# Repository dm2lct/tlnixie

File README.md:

# Schematics and PCB files for the Turmlabor nixie clock kit. 
# Attention: This is a old, buggy version! See the new design on https://github.com/ludwig1992/Nixieclock_kit

Feel free to build your own nixie clock from it.

Features:
  - IN14 nixie tubes but you can adapt many other nixie tubes even if it would not look great
  - ESP12e controller so you can make IoT with it and build your own botnet for world domination if you have enough clocks
  - DS3231 RTC for everyone who does not like IoT and does also not want to be enslaved from AI
  - WS2812B under each nixie tube to make them look more fancy
  - runs from a simple USB charger
  - you can program the controller with your Arduino IDE over USB

But in this version there are a few known issues:

  - wrong footprint of U201 and U202, it should be PQFP44, but of any reason we put TQFP44 on this board. You can solder it but it's not fun. 
  - wrong wiring of U403, you need to wire pin 10 and 11 to pin 18 and 19 and move VCC from pin 18 to pin 20.
  - the high voltage power supply does not work as good as it is supposed to be. This might be a problem with the low input voltage of about 5V

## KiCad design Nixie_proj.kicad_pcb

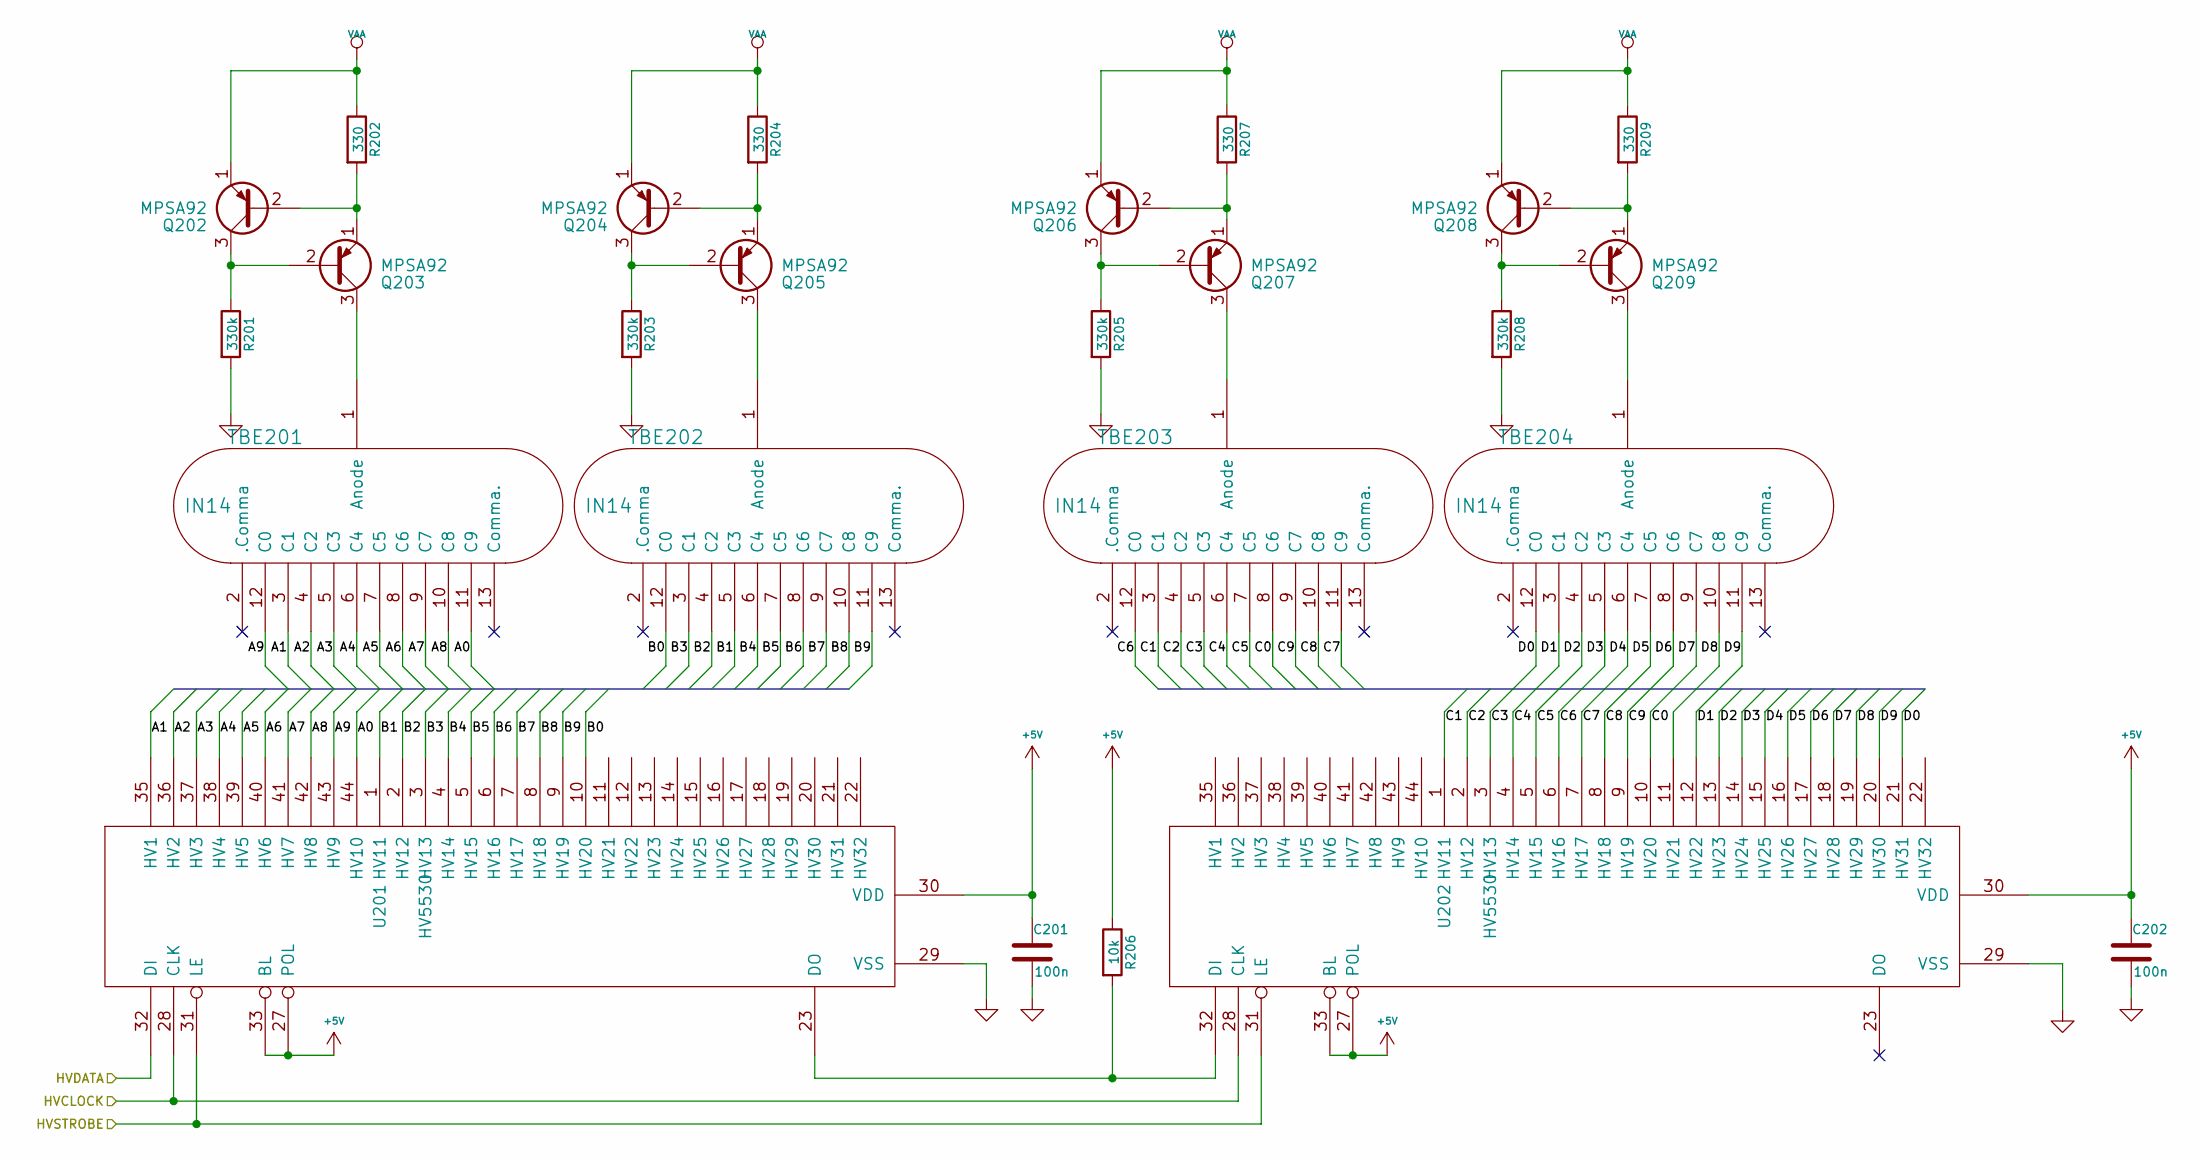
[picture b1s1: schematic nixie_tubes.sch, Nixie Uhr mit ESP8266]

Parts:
C201, C202: 100n; C_0805_HandSoldering
Q202, Q203, Q204, Q205, Q206, Q207, Q208, Q209: MPSA92; TO-92_Molded_Wide_Oval
R201, R203, R205, R208: 330k; R_Axial_DIN0207_L6.3mm_D2.5mm_P10.16mm_Horizontal
R202, R204, R207, R209: 330; R_Axial_DIN0207_L6.3mm_D2.5mm_P10.16mm_Horizontal
R206: 10k; R_0805_HandSoldering
TBE201, TBE202, TBE203, TBE204: IN14; IN-14-mod
U201, U202: HV5530; TQFP-44_10x10mm_Pitch0.8mm

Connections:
+5V: C201.1, C202.1, R206.1, U201.27 (POL), U201.30 (VDD), U201.33 (BL), U202.27 (POL), U202.30 (VDD), U202.33 (BL); also elsewhere on the board
/Microcontroller and clock/HVCLOCK: U201.28 (CLK), U202.28 (CLK); also elsewhere on the board
/Microcontroller and clock/HVDATA: U201.32 (DI); also elsewhere on the board
/Microcontroller and clock/HVSTROBE: U201.31 (LE), U202.31 (LE); also elsewhere on the board
/Tubes with drivers/A0: TBE201.11 (C9), U201.44 (HV10)
/Tubes with drivers/A1: TBE201.3 (C1), U201.35 (HV1)
/Tubes with drivers/A2: TBE201.4 (C2), U201.36 (HV2)
/Tubes with drivers/A3: TBE201.5 (C3), U201.37 (HV3)
/Tubes with drivers/A4: TBE201.6 (C4), U201.38 (HV4)
/Tubes with drivers/A5: TBE201.7 (C5), U201.39 (HV5)
/Tubes with drivers/A6: TBE201.8 (C6), U201.40 (HV6)
/Tubes with drivers/A7: TBE201.9 (C7), U201.41 (HV7)
/Tubes with drivers/A8: TBE201.10 (C8), U201.42 (HV8)
/Tubes with drivers/A9: TBE201.12 (C0), U201.43 (HV9)
/Tubes with drivers/B0: TBE202.12 (C0), U201.10 (HV20)
/Tubes with drivers/B1: TBE202.5 (C3), U201.1 (HV11)
/Tubes with drivers/B2: TBE202.4 (C2), U201.2 (HV12)
/Tubes with drivers/B3: TBE202.3 (C1), U201.3 (HV13)
/Tubes with drivers/B4: TBE202.6 (C4), U201.4 (HV14)
/Tubes with drivers/B5: TBE202.7 (C5), U201.5 (HV15)
/Tubes with drivers/B6: TBE202.8 (C6), U201.6 (HV16)
/Tubes with drivers/B7: TBE202.9 (C7), U201.7 (HV17)
/Tubes with drivers/B8: TBE202.10 (C8), U201.8 (HV18)
/Tubes with drivers/B9: TBE202.11 (C9), U201.9 (HV19)
/Tubes with drivers/C0: TBE203.8 (C6), U202.10 (HV20)
/Tubes with drivers/C1: TBE203.3 (C1), U202.1 (HV11)
/Tubes with drivers/C2: TBE203.4 (C2), U202.2 (HV12)
/Tubes with drivers/C3: TBE203.5 (C3), U202.3 (HV13)
/Tubes with drivers/C4: TBE203.6 (C4), U202.4 (HV14)
/Tubes with drivers/C5: TBE203.7 (C5), U202.5 (HV15)
/Tubes with drivers/C6: TBE203.12 (C0), U202.6 (HV16)
/Tubes with drivers/C7: TBE203.11 (C9), U202.7 (HV17)
/Tubes with drivers/C8: TBE203.10 (C8), U202.8 (HV18)
/Tubes with drivers/C9: TBE203.9 (C7), U202.9 (HV19)
/Tubes with drivers/D0: TBE204.12 (C0), U202.21 (HV31)
/Tubes with drivers/D1: TBE204.3 (C1), U202.12 (HV22)
/Tubes with drivers/D2: TBE204.4 (C2), U202.13 (HV23)
/Tubes with drivers/D3: TBE204.5 (C3), U202.14 (HV24)
/Tubes with drivers/D4: TBE204.6 (C4), U202.15 (HV25)
/Tubes with drivers/D5: TBE204.7 (C5), U202.16 (HV26)
/Tubes with drivers/D6: TBE204.8 (C6), U202.17 (HV27)
/Tubes with drivers/D7: TBE204.9 (C7), U202.18 (HV28)
/Tubes with drivers/D8: TBE204.10 (C8), U202.19 (HV29)
/Tubes with drivers/D9: TBE204.11 (C9), U202.20 (HV30)
GND: C201.2, C202.2, R201.2, R203.2, R205.2, R208.2, U201.29 (VSS), U202.29 (VSS); also elsewhere on the board
unnamed: Q202.2 (B), Q203.1 (E), R202.2
unnamed: Q202.3 (C), Q203.2 (B), R201.1
unnamed: Q203.3 (C), TBE201.1 (Anode)
unnamed: Q204.2 (B), Q205.1 (E), R204.2
unnamed: Q204.3 (C), Q205.2 (B), R203.1
unnamed: Q205.3 (C), TBE202.1 (Anode)
unnamed: Q206.2 (B), Q207.1 (E), R207.2
unnamed: Q206.3 (C), Q207.2 (B), R205.1
unnamed: Q207.3 (C), TBE203.1 (Anode)
unnamed: Q208.2 (B), Q209.1 (E), R209.2
unnamed: Q208.3 (C), Q209.2 (B), R208.1
unnamed: Q209.3 (C), TBE204.1 (Anode)
unnamed: R206.2, U201.23 (DO), U202.32 (DI)
VAA: Q202.1 (E), Q204.1 (E), Q206.1 (E), Q208.1 (E), R202.1, R204.1, R207.1, R209.1; also elsewhere on the board

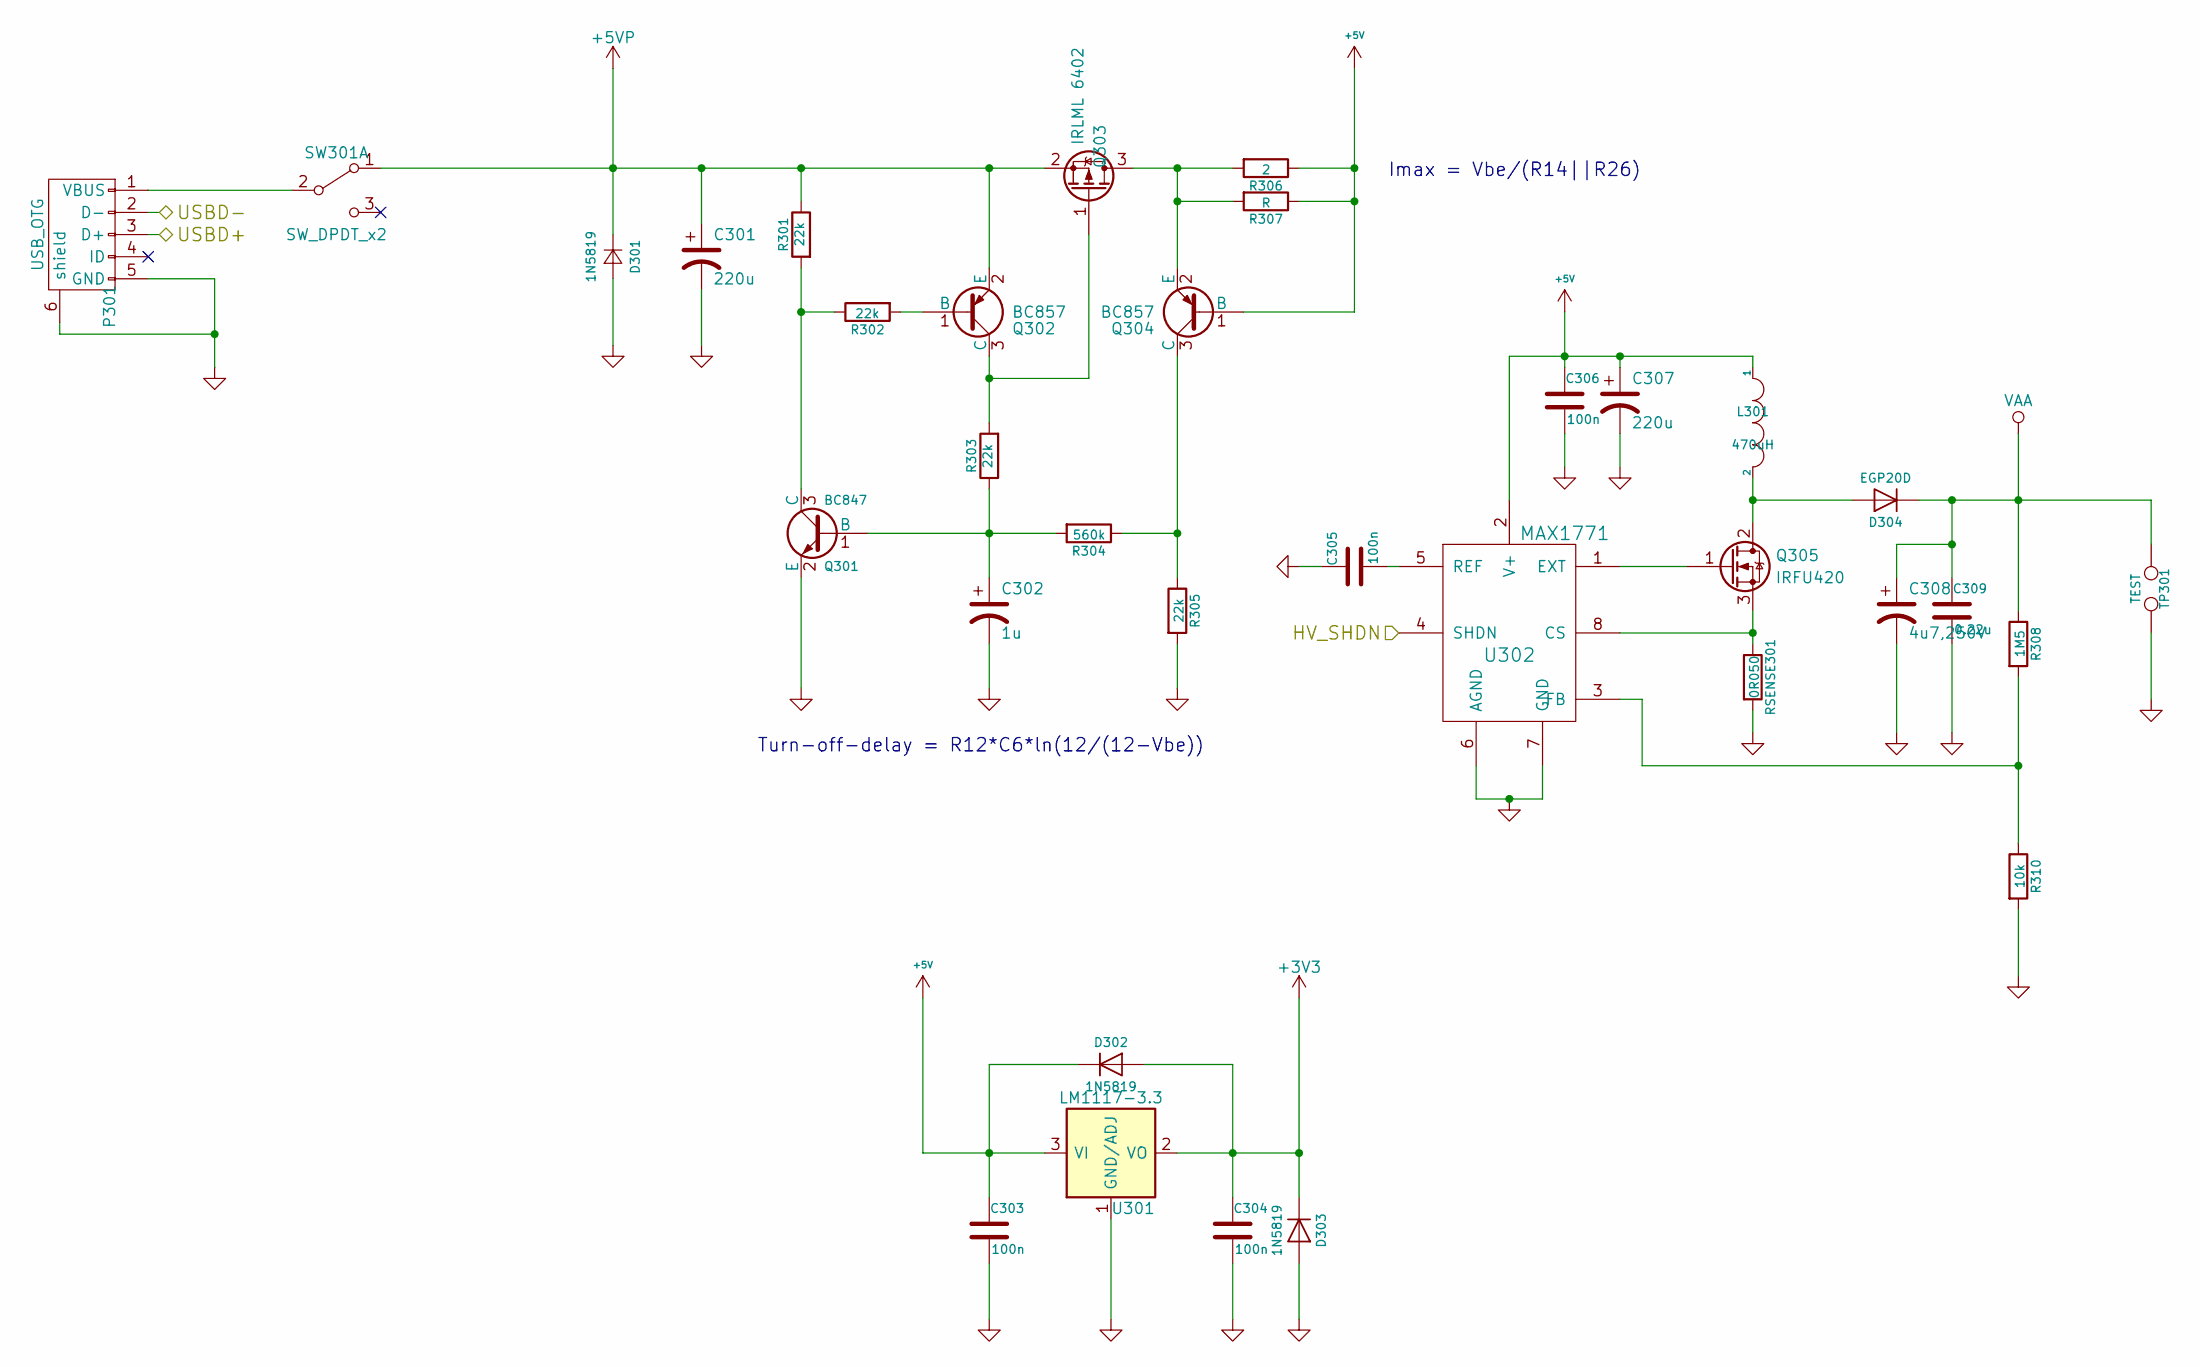
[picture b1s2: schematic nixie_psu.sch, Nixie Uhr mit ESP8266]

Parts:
C301, C307: 220u; CP_Elec_6.3x7.7
C302: 1u; CP_Elec_4x5.7
C303, C304, C305, C306: 100n; C_0805_HandSoldering
C308: 4u7,250V; CP_Radial_D10.0mm_P7.50mm
C309: 0.22u; C_Rect_L13.0mm_W6.0mm_P10.00mm_FKS3_FKP3_MKS4
D301, D302, D303: 1N5819; D_MiniMELF_Handsoldering
D304: EGP20D; D_MELF-RM10_Universal_Handsoldering
L301: 470uH; L_Radial_D8.7mm_P5.00mm_Fastron_07HCP
P301: USB_OTG; USB_Mini-B
Q301: BC847; SOT-23W_Handsoldering
Q302, Q304: BC857; SOT-23W_Handsoldering
Q303: IRLML 6402; SOT-23W_Handsoldering
Q305: IRFU420; TO-252-3_TabPin4
R301, R302, R303, R305: 22k; R_0805_HandSoldering
R304: 560k; R_0805_HandSoldering
R306: 2; R_1210_HandSoldering
R307: R; R_1210_HandSoldering
R308: 1M5; R_0805_HandSoldering
R310: 10k; R_0805_HandSoldering
RSENSE301: 0R050; R_1210_HandSoldering
SW301: SW_DPDT_x2; SW_CuK_OS102011MA1QN1_SPDT_Angled
TP301: TEST; R_1210_HandSoldering
U301: LM1117-3.3; TO-252-2
U302: MAX1771; DIP-8_W7.62mm_LongPads

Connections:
+3V3: C304.1, D302.2 (A), D303.1 (K), U301.2 (VO), U301.4 (VO); also elsewhere on the board
+5V: C303.1, C306.1, C307.1, D302.1 (K), L301.1, Q304.1 (B), R306.1, R307.1, U301.3 (VI), U302.2 (V+); also elsewhere on the board
+5VP: C301.1, D301.1 (K), Q302.2 (E), Q303.2 (S), R301.1, SW301.1 (A)
/Microcontroller and clock/HV_SHDN: U302.4 (SHDN); also elsewhere on the board
/Microcontroller and clock/USBD+: P301.3 (D+); also elsewhere on the board
/Microcontroller and clock/USBD-: P301.2 (D-); also elsewhere on the board
GND: C301.2, C302.2, C303.2, C304.2, C305.1, C306.2, C307.2, C308.2, C309.2, D301.2 (A), D303.2 (A), P301.5 (GND), P301.6 (shield), Q301.2 (E), R305.2, R310.2, RSENSE301.2, TP301.2, U301.1 (GND/ADJ), U302.6 (AGND), U302.7 (GND); also elsewhere on the board
unnamed: C302.1, Q301.1 (B), R303.1, R304.2
unnamed: C305.2, U302.5 (REF)
unnamed: D304.2 (A), L301.2, Q305.2 (D)
unnamed: P301.1 (VBUS), SW301.2 (B)
unnamed: Q301.3 (C), R301.2, R302.1
unnamed: Q302.1 (B), R302.2
unnamed: Q302.3 (C), Q303.1 (G), R303.2
unnamed: Q303.3 (D), Q304.2 (E), R306.2, R307.2
unnamed: Q304.3 (C), R304.1, R305.1
unnamed: Q305.1 (G), U302.1 (EXT)
unnamed: Q305.3 (S), RSENSE301.1, U302.8 (CS)
unnamed: R308.2, R310.1, U302.3 (FB)
VAA: C308.1, C309.1, D304.1 (K), R308.1, TP301.1; also elsewhere on the board

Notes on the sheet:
Imax = Vbe/(R14||R26)
Turn-off-delay = R12*C6*ln(12/(12-Vbe))

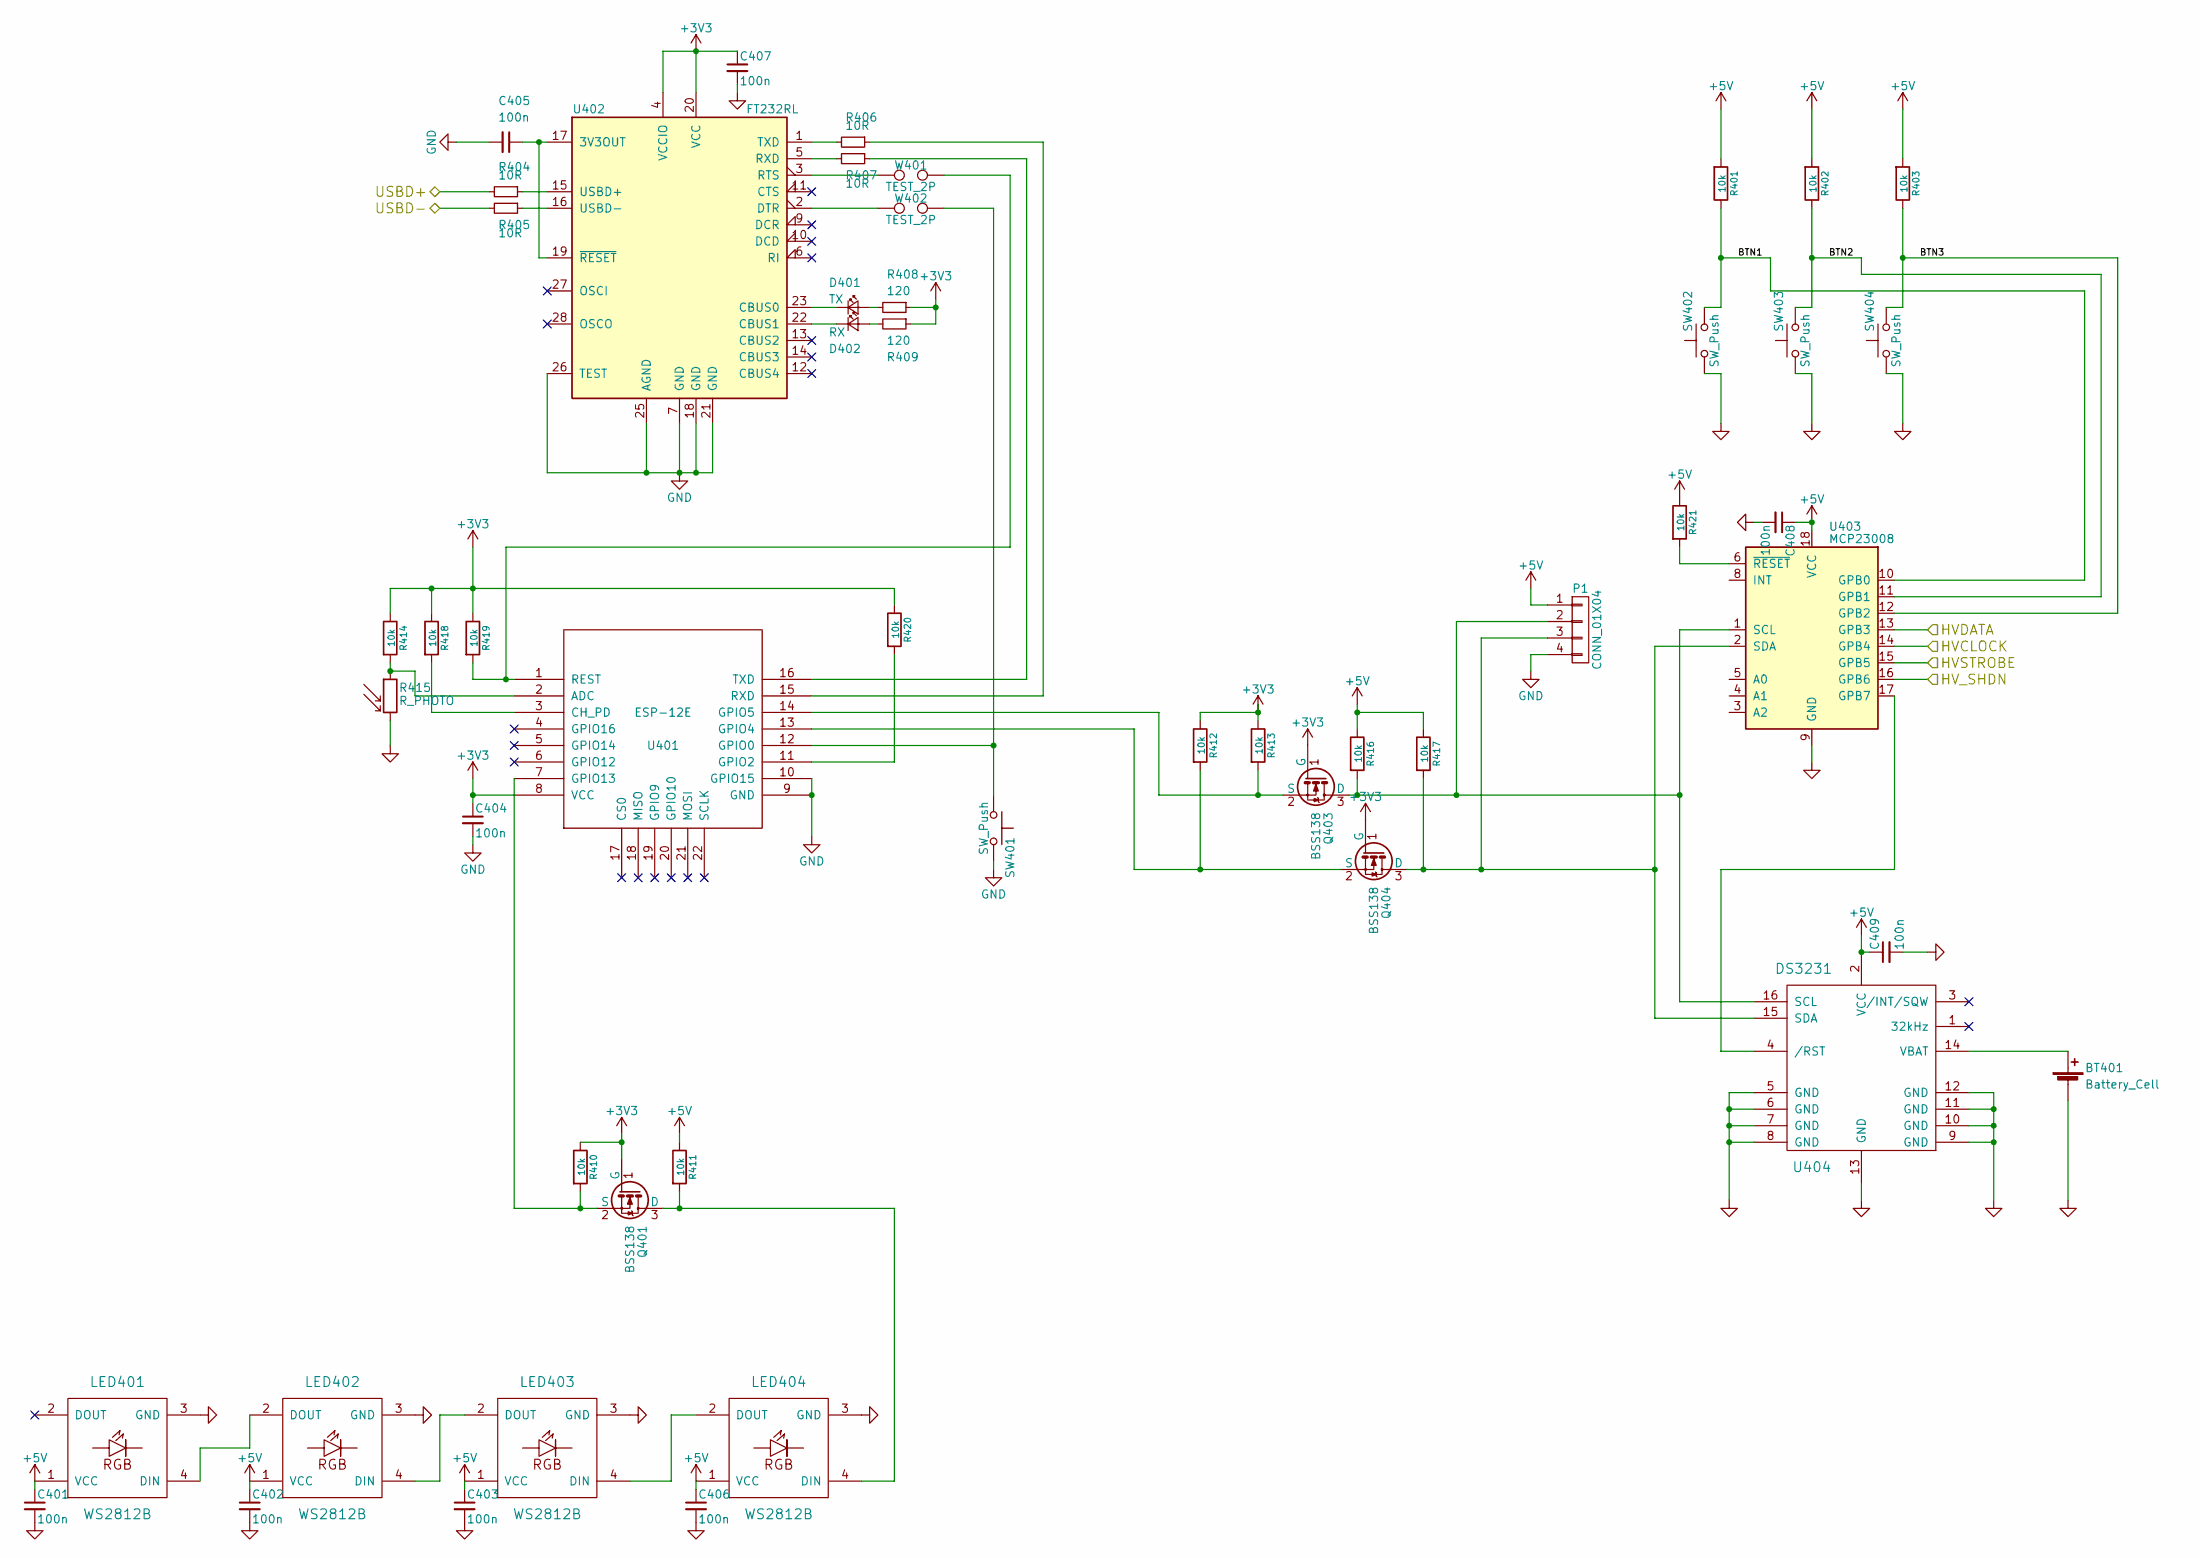
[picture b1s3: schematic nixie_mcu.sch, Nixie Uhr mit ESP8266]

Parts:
BT401: Battery_Cell; Keystone_3034_1x20mm-CoinCell
C401, C402, C403, C404, C405, C406, C407, C408, C409: 100n; C_0805_HandSoldering
D401: TX; LED_0805_HandSoldering
D402: RX; LED_0805_HandSoldering
LED401, LED402, LED403, LED404: WS2812B
P1: CONN_01X04; Pin_Header_Straight_1x04_Pitch2.54mm
Q401, Q403, Q404: BSS138; SOT-23W_Handsoldering
R401, R402, R403, R410, R411, R412, R413, R414, R416, R417, R418, R419, R420, R421: 10k; R_0805_HandSoldering
R404, R405, R406, R407: 10R; R_0805_HandSoldering
R408, R409: 120; R_0805_HandSoldering
R415: R_PHOTO; R_Axial_DIN0207_L6.3mm_D2.5mm_P5.08mm_Vertical
SW401: SW_Push; SW_PUSH_6mm_h4.3mm
SW402, SW403, SW404: SW_Push; SW_Tactile_SPST_Angled_PTS645Vx39-2LFS
U401: ESP-12E; ESP-12E_SMD
U402: FT232RL; SSOP-28_5.3x10.2mm_Pitch0.65mm
U403: MCP23008; SSOP-20_5.3x7.2mm_Pitch0.65mm
U404: DS3231; SOIC-16W_7.5x10.3mm_Pitch1.27mm
W401, W402: TEST_2P; R_0805_HandSoldering

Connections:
+3V3: C404.1, C407.1, Q401.1 (G), Q403.1 (G), Q404.1 (G), R408.1, R409.1, R410.1, R412.1, R413.1, R414.1, R418.1, R419.1, R420.1, U401.8 (VCC), U402.4 (VCCIO), U402.20 (VCC); also elsewhere on the board
+5V: C401.1, C402.1, C403.1, C406.1, C408.1, C409.1, LED401.1 (VCC), LED402.1 (VCC), LED403.1 (VCC), LED404.1 (VCC), P1.1, R401.2, R402.2, R403.2, R411.1, R416.1, R417.1, R421.1, U403.18 (VCC), U404.2 (VCC); also elsewhere on the board
/Microcontroller and clock/BTN1: R401.1, SW402.2, U403.10 (GPB0)
/Microcontroller and clock/BTN2: R402.1, SW403.2, U403.11 (GPB1)
/Microcontroller and clock/BTN3: R403.1, SW404.2, U403.12 (GPB2)
/Microcontroller and clock/HVCLOCK: U403.14 (GPB4); also elsewhere on the board
/Microcontroller and clock/HVDATA: U403.13 (GPB3); also elsewhere on the board
/Microcontroller and clock/HVSTROBE: U403.15 (GPB5); also elsewhere on the board
/Microcontroller and clock/HV_SHDN: U403.16 (GPB6); also elsewhere on the board
/Microcontroller and clock/USBD+: R404.2; also elsewhere on the board
/Microcontroller and clock/USBD-: R405.2; also elsewhere on the board
GND: BT401.2 (-), C401.2, C402.2, C403.2, C404.2, C405.2, C406.2, C407.2, C408.2, C409.2, LED401.3 (GND), LED402.3 (GND), LED403.3 (GND), LED404.3 (GND), P1.4, R415.2, SW401.2, SW402.1, SW403.1, SW404.1, U401.9 (GND), U401.10 (GPIO15), U402.7 (GND), U402.18 (GND), U402.21 (GND), U402.25 (AGND), U402.26 (TEST), U403.9 (GND), U404.5 (GND), U404.6 (GND), U404.7 (GND), U404.8 (GND), U404.9 (GND), U404.10 (GND), U404.11 (GND), U404.12 (GND), U404.13 (GND); also elsewhere on the board
unnamed 53: BT401.1 (+), U404.14 (VBAT); also elsewhere on the board
unnamed: C405.1, U402.17 (3V3OUT), U402.19 (~RESET~)
unnamed 58: D401.1 (K), U402.23 (CBUS0); also elsewhere on the board
unnamed 59: D401.2 (A), R408.2; also elsewhere on the board
unnamed 60: D402.1 (K), U402.22 (CBUS1); also elsewhere on the board
unnamed 61: D402.2 (A), R409.2; also elsewhere on the board
unnamed: LED401.4 (DIN), LED402.2 (DOUT)
unnamed: LED402.4 (DIN), LED403.2 (DOUT)
unnamed: LED403.4 (DIN), LED404.2 (DOUT)
unnamed: LED404.4 (DIN), Q401.3 (D), R411.2
unnamed 66: P1.2, Q403.3 (D), R416.2, U403.1 (SCL), U404.16 (SCL); also elsewhere on the board
unnamed 67: P1.3, Q404.3 (D), R417.2, U403.2 (SDA), U404.15 (SDA); also elsewhere on the board
unnamed: Q401.2 (S), R410.2, U401.7 (GPIO13)
unnamed: Q403.2 (S), R413.2, U401.14 (GPIO5)
unnamed: Q404.2 (S), R412.2, U401.13 (GPIO4)
unnamed: R404.1, U402.15 (USBD+)
unnamed: R405.1, U402.16 (USBD-)
unnamed: R406.1, U401.15 (RXD)
unnamed: R406.2, U402.1 (TXD)
unnamed: R407.1, U401.16 (TXD)
unnamed: R407.2, U402.5 (RXD)
unnamed: R414.2, R415.1, U401.2 (ADC)
unnamed: R418.2, U401.3 (CH_PD)
unnamed: R419.2, U401.1 (REST), W401.2
unnamed: R420.2, U401.11 (GPIO2)
unnamed: R421.2, U403.6 (~RESET)
unnamed 104: SW401.1, U401.12 (GPIO0), W402.2; also elsewhere on the board
unnamed: U402.2 (DTR), W402.1
unnamed: U402.3 (RTS), W401.1
unnamed: U403.17 (GPB7), U404.4 (/RST)

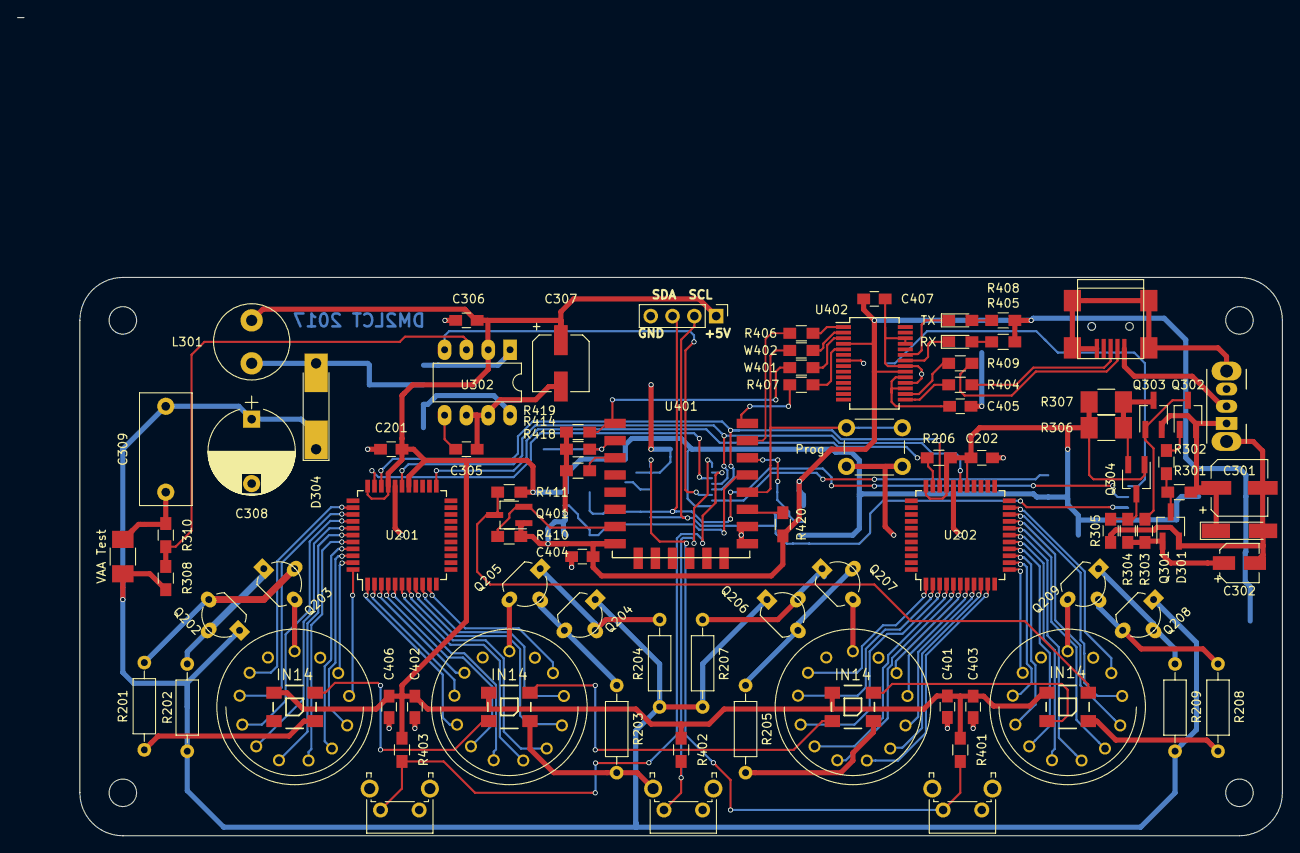
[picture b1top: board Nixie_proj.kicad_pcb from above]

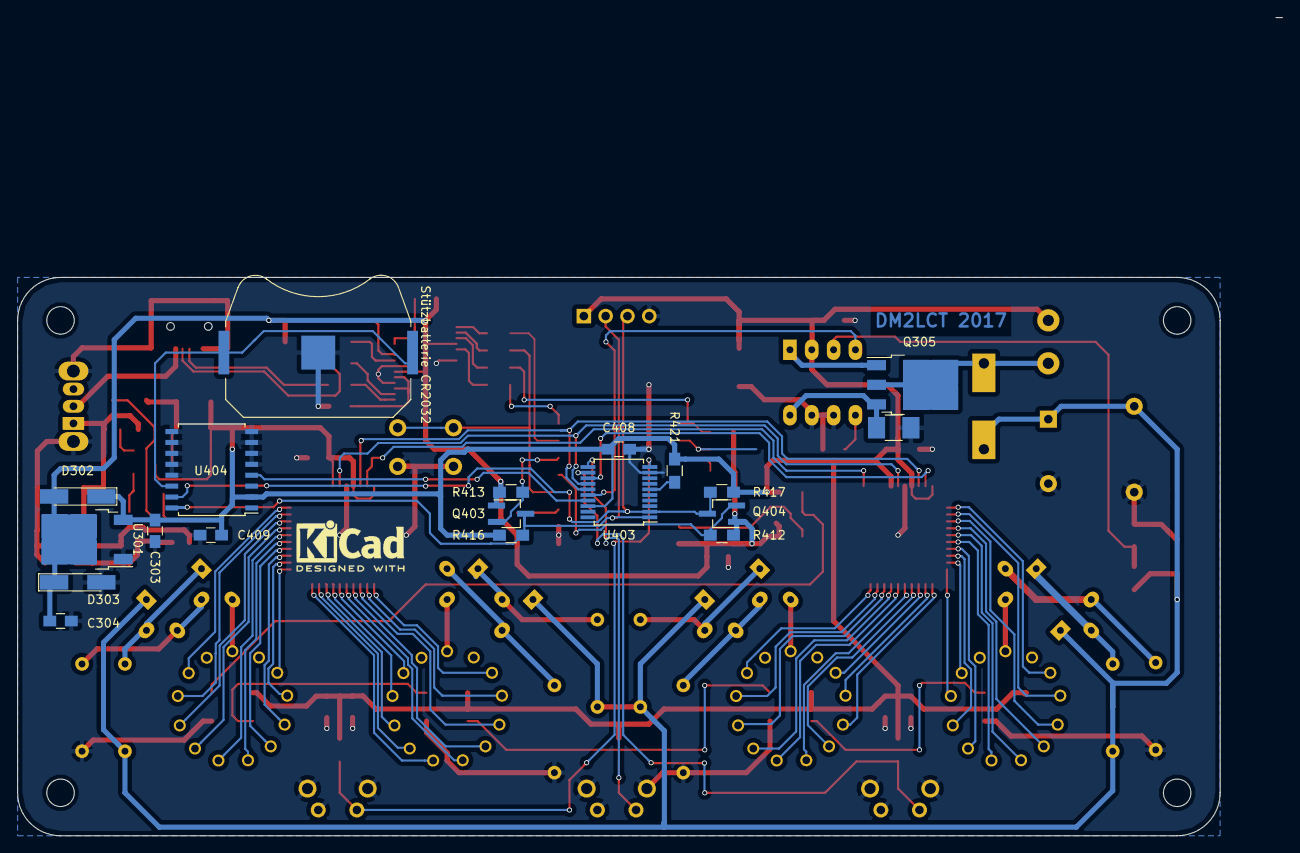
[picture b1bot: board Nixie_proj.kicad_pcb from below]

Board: 2 copper layers, 147.2 x 95.2 mm, 109 parts (19 on the bottom side), 109 nets.

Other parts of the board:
Prog: SW_Push; SW_PUSH_6mm_h4.3mm
RX: RX; LED_0805_HandSoldering
SPI Interface: CONN_01X04; Pin_Header_Straight_1x04_Pitch2.54mm
Stützbatterie CR2032: Battery_Cell; Keystone_3034_1x20mm-CoinCell
TX: TX; LED_0805_HandSoldering
VAA Test: TEST; R_1210_HandSoldering

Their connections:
+5V: SPI Interface.1; also elsewhere on the board
GND: Prog.2, SPI Interface.4, Stützbatterie CR2032.2, VAA Test.2; also elsewhere on the board
unnamed 53: Stützbatterie CR2032.1; also elsewhere on the board
unnamed 58: TX.1; also elsewhere on the board
unnamed 59: TX.2; also elsewhere on the board
unnamed 60: RX.1; also elsewhere on the board
unnamed 61: RX.2; also elsewhere on the board
unnamed 66: SPI Interface.2; also elsewhere on the board
unnamed 67: SPI Interface.3; also elsewhere on the board
unnamed 104: Prog.1; also elsewhere on the board
VAA: VAA Test.1; also elsewhere on the board
